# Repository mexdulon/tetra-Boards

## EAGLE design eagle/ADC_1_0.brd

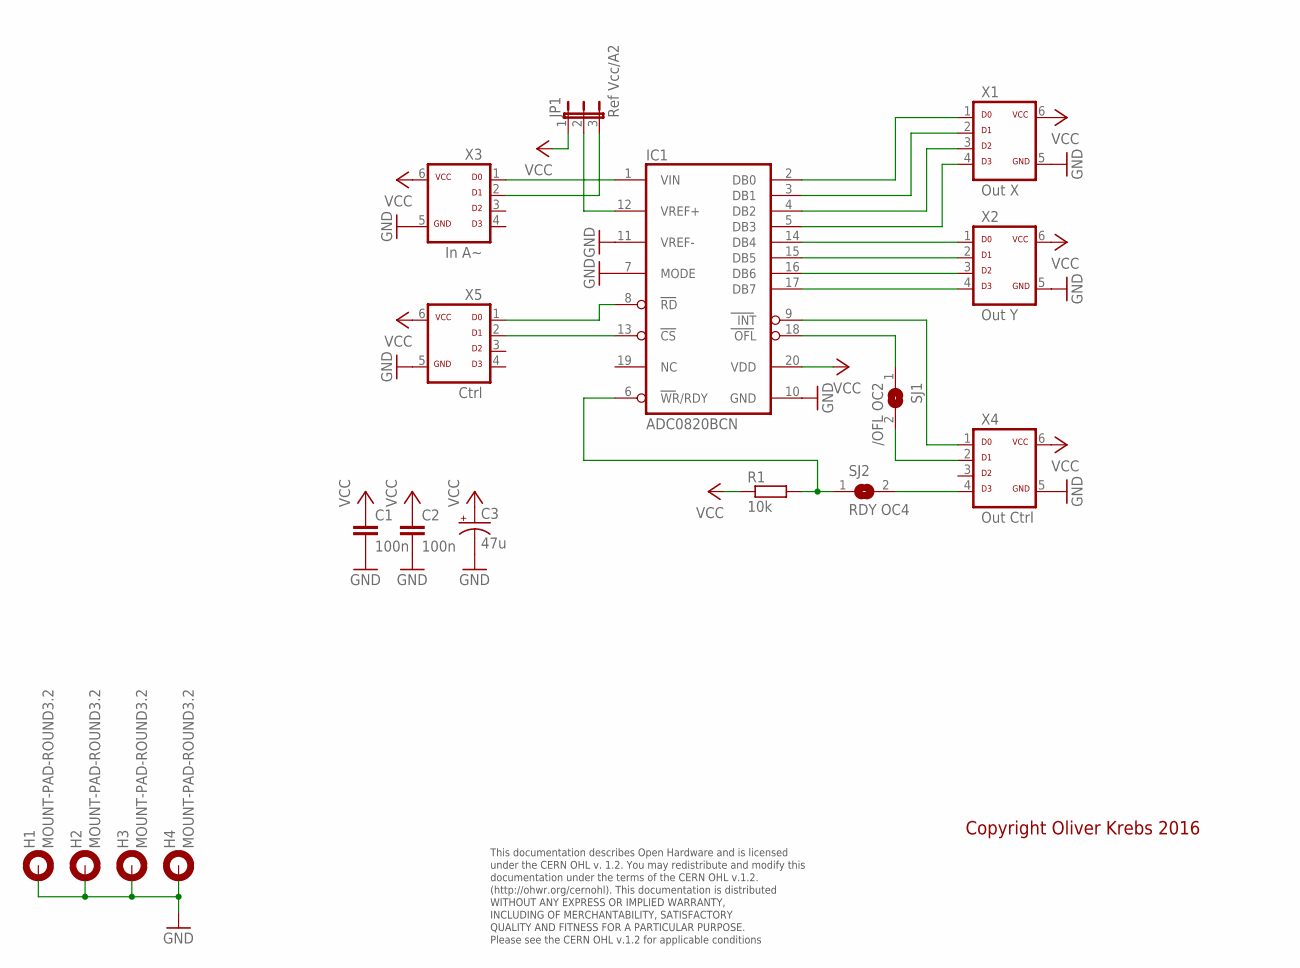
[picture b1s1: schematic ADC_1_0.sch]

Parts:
C1, C2: 100n; CAP-PTH-5MM
C3: 47u; CPOL-RADIAL-100UF-25V
H1, H2, H3, H4: MOUNT-PAD-ROUND3.2; 3,2-PAD
IC1: ADC0820BCN; DIL20
JP1: Ref Vcc/A2; JP2-U
R1: 10k; 0207/10
SJ1: /OFL OC2; SJ
SJ2: RDY OC4; SJ
X1: Out X; ML-6
X2: Out Y; ML-6
X3: In A~; ML-6
X4: Out Ctrl; ML-6
X5: Ctrl; ML-6

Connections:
GND: C1.2, C2.2, C3.2 (-), H1.B3,2, H2.B3,2, H3.B3,2, H4.B3,2, IC1.7 (MODE), IC1.10 (GND), IC1.11 (VREF-), X1.5, X2.5, X3.5, X4.5, X5.5
unnamed: IC1.9 (INT), X4.1
unnamed: SJ1.2, X4.2
unnamed: IC1.2 (DB0), X1.1
unnamed: IC1.3 (DB1), X1.2
unnamed: IC1.4 (DB2), X1.3
unnamed: IC1.5 (DB3), X1.4
unnamed: IC1.14 (DB4), X2.1
unnamed: IC1.15 (DB5), X2.2
unnamed: IC1.16 (DB6), X2.3
unnamed: IC1.17 (DB7), X2.4
unnamed: IC1.1 (VIN), X3.1
unnamed: SJ2.2, X4.4
unnamed: IC1.13 (CS), X5.2
unnamed: IC1.12 (VREF+), JP1.2
unnamed: IC1.8 (RD), X5.1
unnamed: JP1.3, X3.2
unnamed: IC1.6 (WR/RDY), R1.2, SJ2.1
unnamed: IC1.18 (OFL), SJ1.1
VCC: C1.1, C2.1, C3.1 (+), IC1.20 (VDD), JP1.1, R1.1, X1.6, X2.6, X3.6, X4.6, X5.6

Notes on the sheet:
This documentation describes Open Hardware and is licensed under the CERN OHL v. 1.2. You may redistribute and modify this documentation under the terms of the CERN OHL v.1.2. (http://ohwr.org/cernohl). This documentation is distributed WITHOUT ANY EXPRESS OR IMPLIED WARRANTY, INCLUDING OF MERCHANT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
Copyright Oliver Krebs 2016

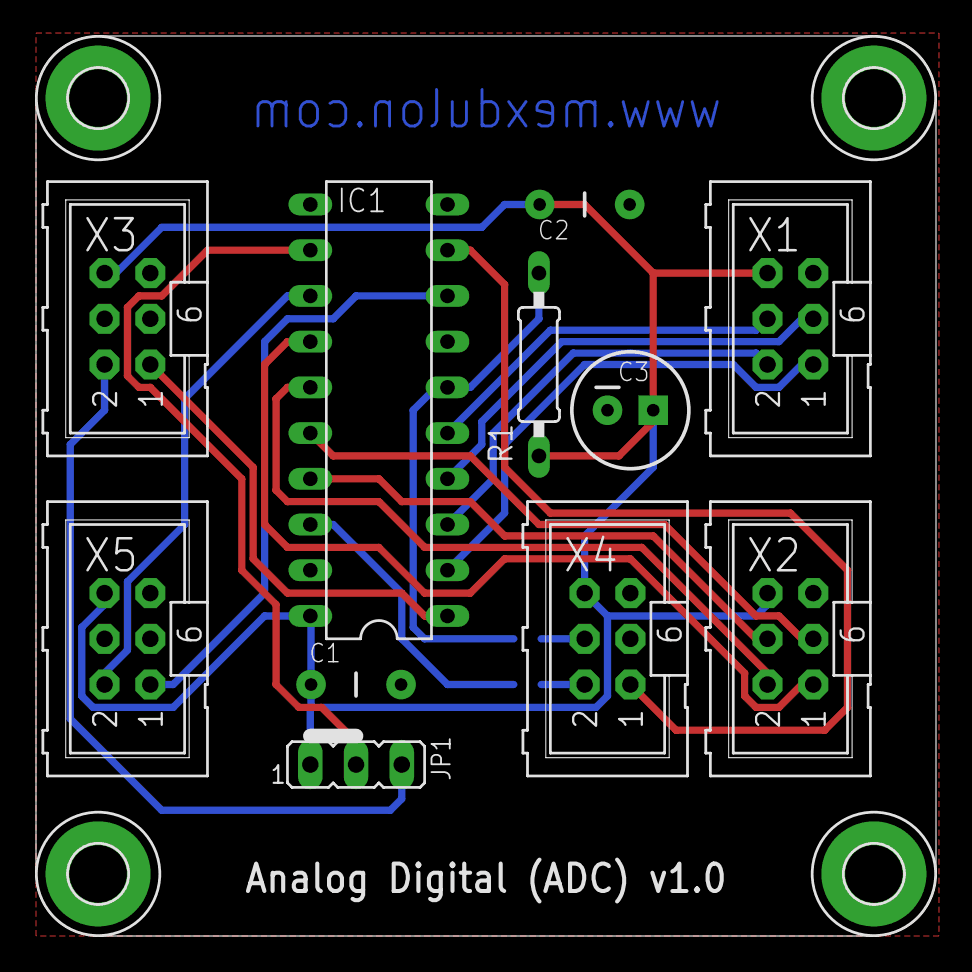
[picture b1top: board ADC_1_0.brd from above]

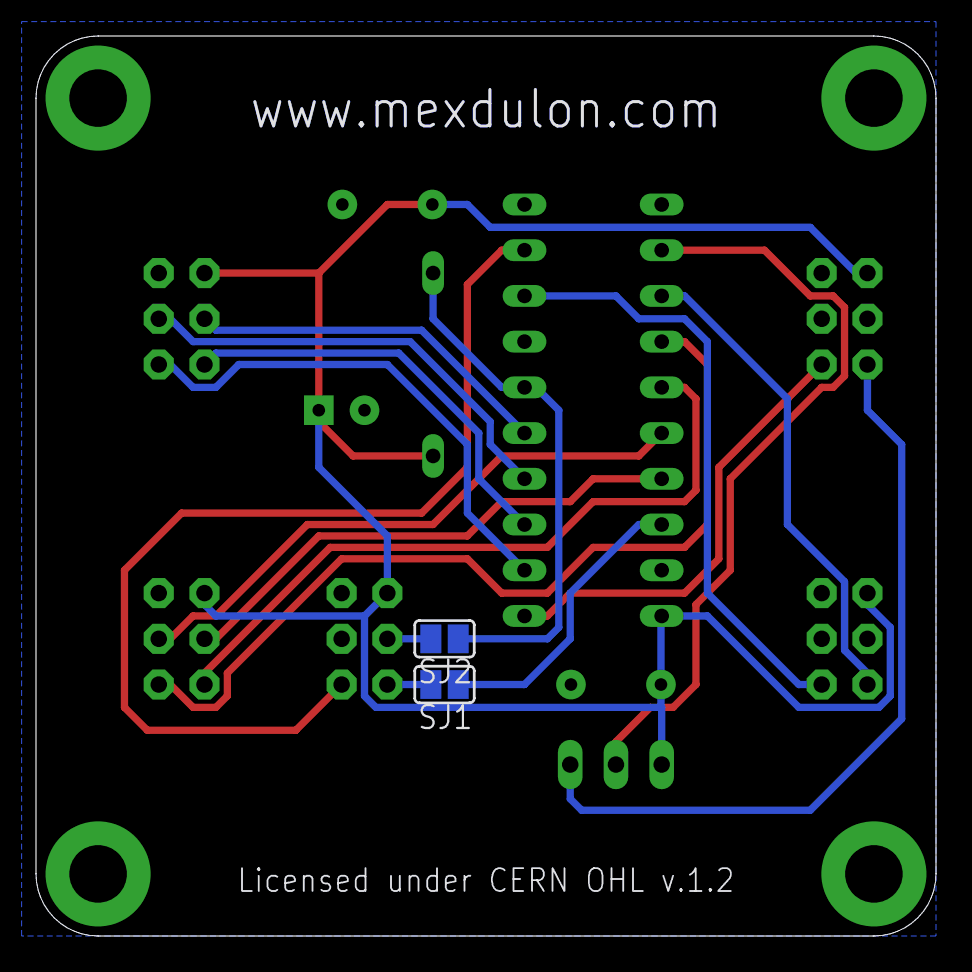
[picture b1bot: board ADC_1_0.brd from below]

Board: 2 copper layers, 50.0 x 50.0 mm, 17 parts (2 on the bottom side), 20 nets.

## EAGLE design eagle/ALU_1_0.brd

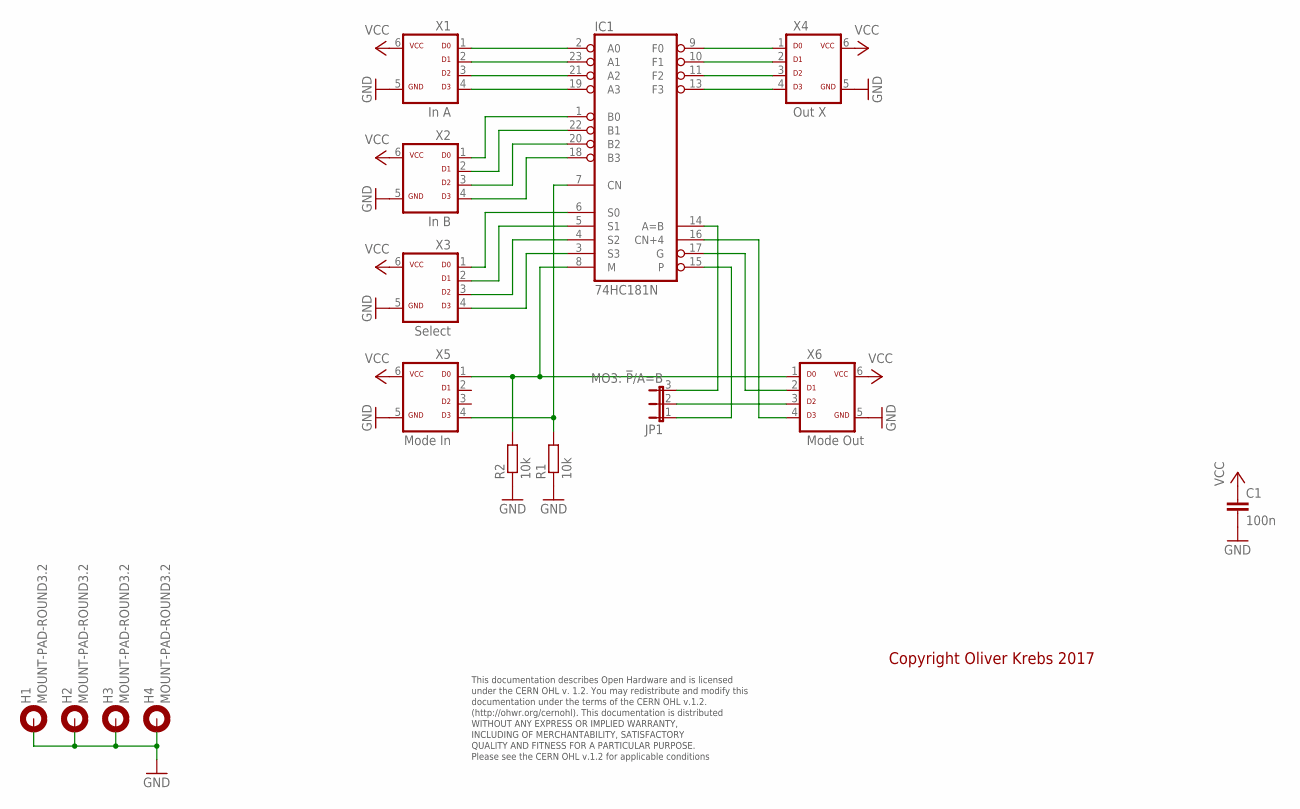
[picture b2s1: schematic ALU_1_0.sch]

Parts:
C1: 100n; C050-025X075
H1, H2, H3, H4: MOUNT-PAD-ROUND3.2; 3,2-PAD
IC1: 74HC181N; DIL24-6
JP1: MO3: !P!/A=B; JP2
R1, R2: 10k; 0207/10
X1: In A; ML-6
X2: In B; ML-6
X3: Select; ML-6
X4: Out X; ML-6
X5: Mode In; ML-6
X6: Mode Out; ML-6

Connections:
GND: C1.2, H1.B3,2, H2.B3,2, H3.B3,2, H4.B3,2, IC1.12 (GND), R1.1, R2.1, X1.5, X2.5, X3.5, X4.5, X5.5, X6.5
unnamed: IC1.9 (F0), X4.1
unnamed: IC1.10 (F1), X4.2
unnamed: IC1.11 (F2), X4.3
unnamed: IC1.13 (F3), X4.4
unnamed: IC1.2 (A0), X1.1
unnamed: IC1.23 (A1), X1.2
unnamed: IC1.21 (A2), X1.3
unnamed: IC1.19 (A3), X1.4
unnamed: IC1.1 (B0), X2.1
unnamed: IC1.22 (B1), X2.2
unnamed: IC1.20 (B2), X2.3
unnamed: IC1.18 (B3), X2.4
unnamed: IC1.6 (S0), X3.1
unnamed: IC1.5 (S1), X3.2
unnamed: IC1.4 (S2), X3.3
unnamed: IC1.3 (S3), X3.4
unnamed: IC1.8 (M), R2.2, X5.1, X6.1
unnamed: IC1.7 (CN), R1.2, X5.4
unnamed: IC1.16 (CN+4), X6.4
unnamed: IC1.15, JP1.1
unnamed: JP1.2, X6.3
unnamed: IC1.14 (A=B), JP1.3
unnamed: IC1.17 (G), X6.2
VCC: C1.1, IC1.24 (VCC), X1.6, X2.6, X3.6, X4.6, X5.6, X6.6

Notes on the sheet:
This documentation describes Open Hardware and is licensed under the CERN OHL v. 1.2. You may redistribute and modify this documentation under the terms of the CERN OHL v.1.2. (http://ohwr.org/cernohl). This documentation is distributed WITHOUT ANY EXPRESS OR IMPLIED WARRANTY, INCLUDING OF MERCHANT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
Copyright Oliver Krebs 2017

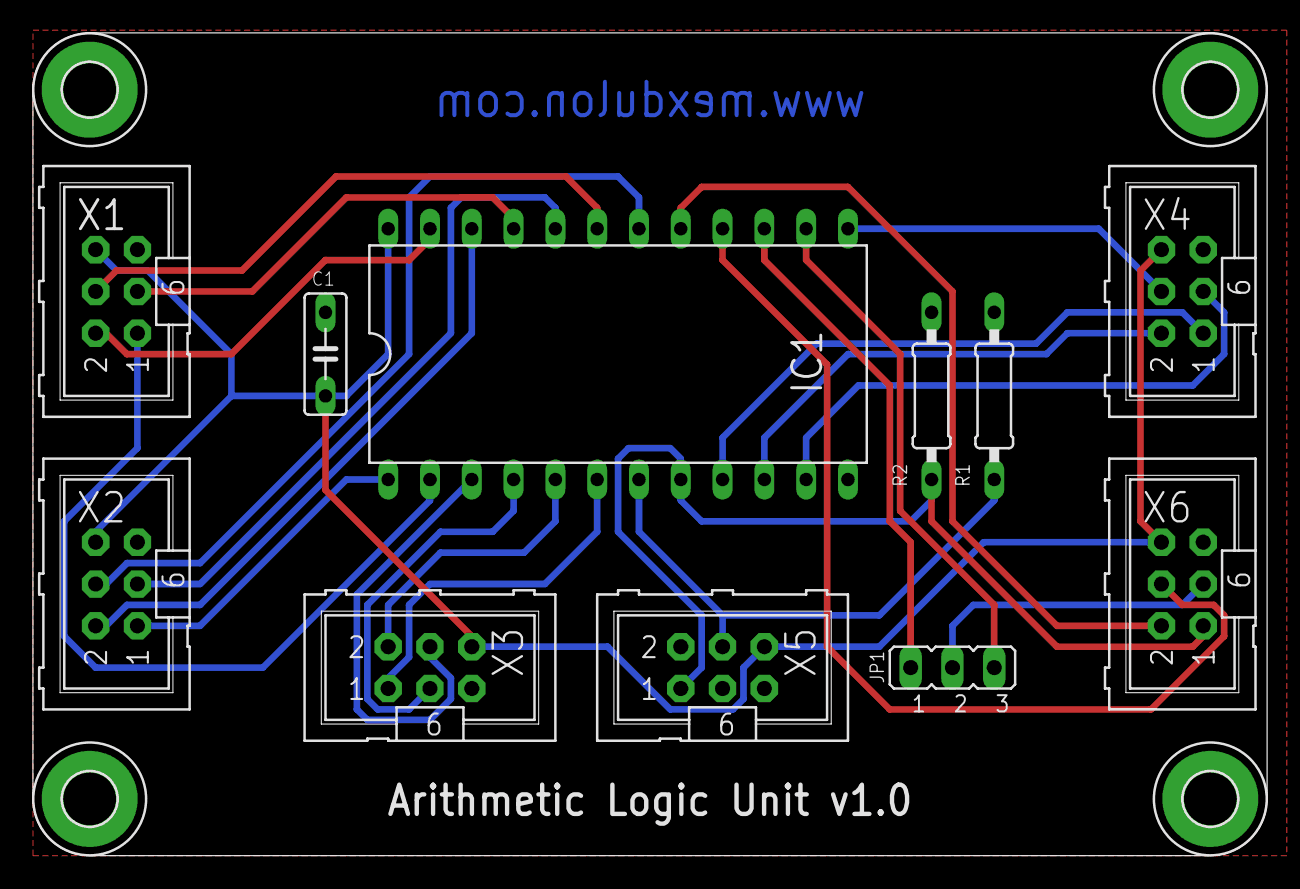
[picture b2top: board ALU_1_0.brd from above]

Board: 2 copper layers, 75.0 x 50.0 mm, 15 parts (0 on the bottom side), 25 nets.

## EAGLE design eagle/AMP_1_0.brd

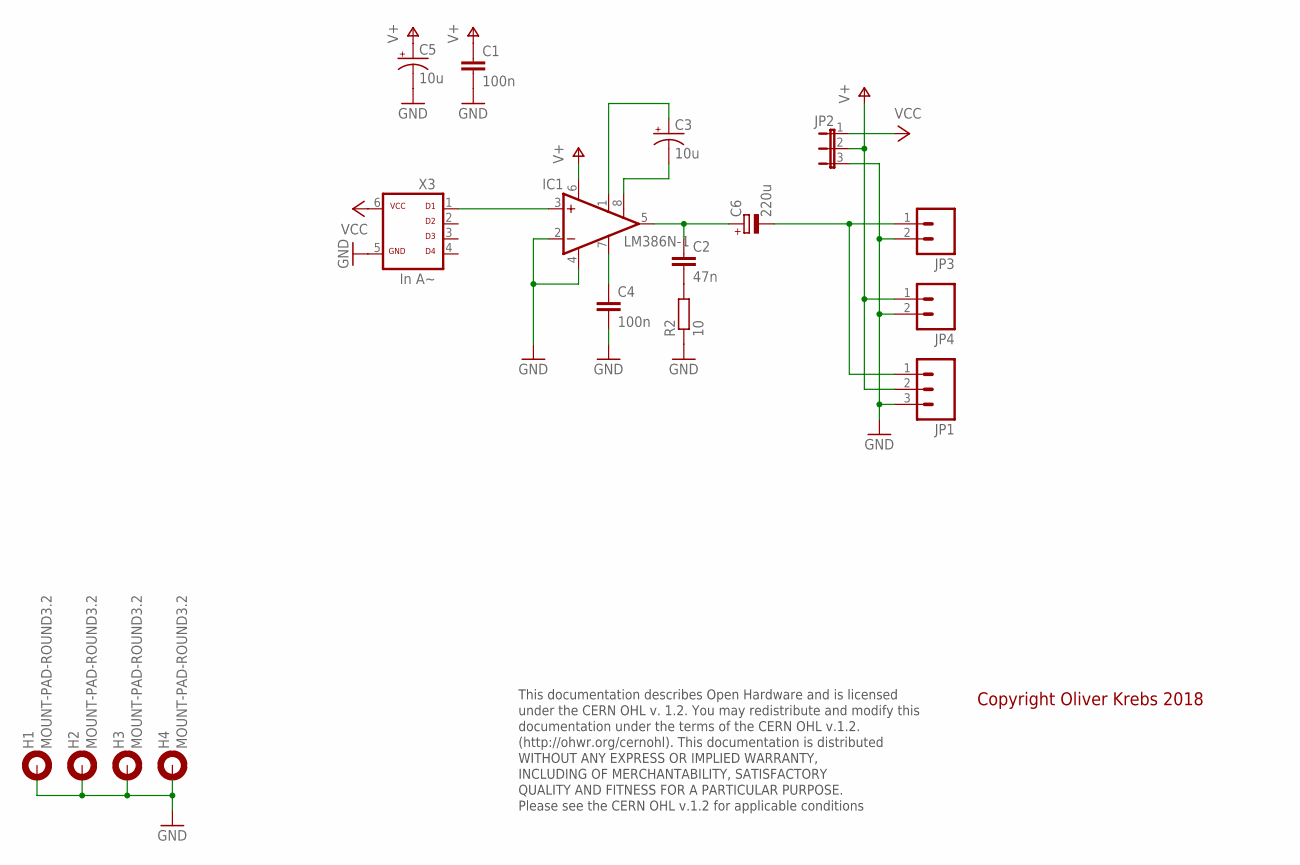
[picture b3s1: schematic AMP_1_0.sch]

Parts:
C1, C4: 100n; C050-025X075
C2: 47n; C050-025X075
C3, C5: 10u; CPOL-RADIAL-10UF-25V
C6: 220u; E3,5-8
H1, H2, H3, H4: MOUNT-PAD-ROUND3.2; 3,2-PAD
IC1: LM386N-1; DIL08
JP1: M03PTH; 1X03
JP2: JP2EJP2-U; JP2-U
JP3, JP4: M021.3MM-5.08; 1X02_BIG_5.08
R2: 10; 0207/10
X3: In A~; ML-6

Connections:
GND: C1.2, C4.2, C5.2 (-), H1.B3,2, H2.B3,2, H3.B3,2, H4.B3,2, IC1.2 (-IN), IC1.4 (GND), JP1.3, JP2.3, JP3.2, JP4.2, R2.1, X3.5
unnamed: C3.2 (-), IC1.8 (GAIN)
unnamed: C3.1 (+), IC1.1 (GAIN)
unnamed: IC1.3 (+IN), X3.1
unnamed: C4.1, IC1.7 (BYPASS)
unnamed: C2.1, C6.+, IC1.5 (OUT)
unnamed: C2.2, R2.2
unnamed: C6.-, JP1.1, JP3.1
V+: C1.1, C5.1 (+), IC1.6 (VS), JP1.2, JP2.2, JP4.1
VCC: JP2.1, X3.6

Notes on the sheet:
This documentation describes Open Hardware and is licensed under the CERN OHL v. 1.2. You may redistribute and modify this documentation under the terms of the CERN OHL v.1.2. (http://ohwr.org/cernohl). This documentation is distributed WITHOUT ANY EXPRESS OR IMPLIED WARRANTY, INCLUDING OF MERCHANT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
Copyright Oliver Krebs 2018

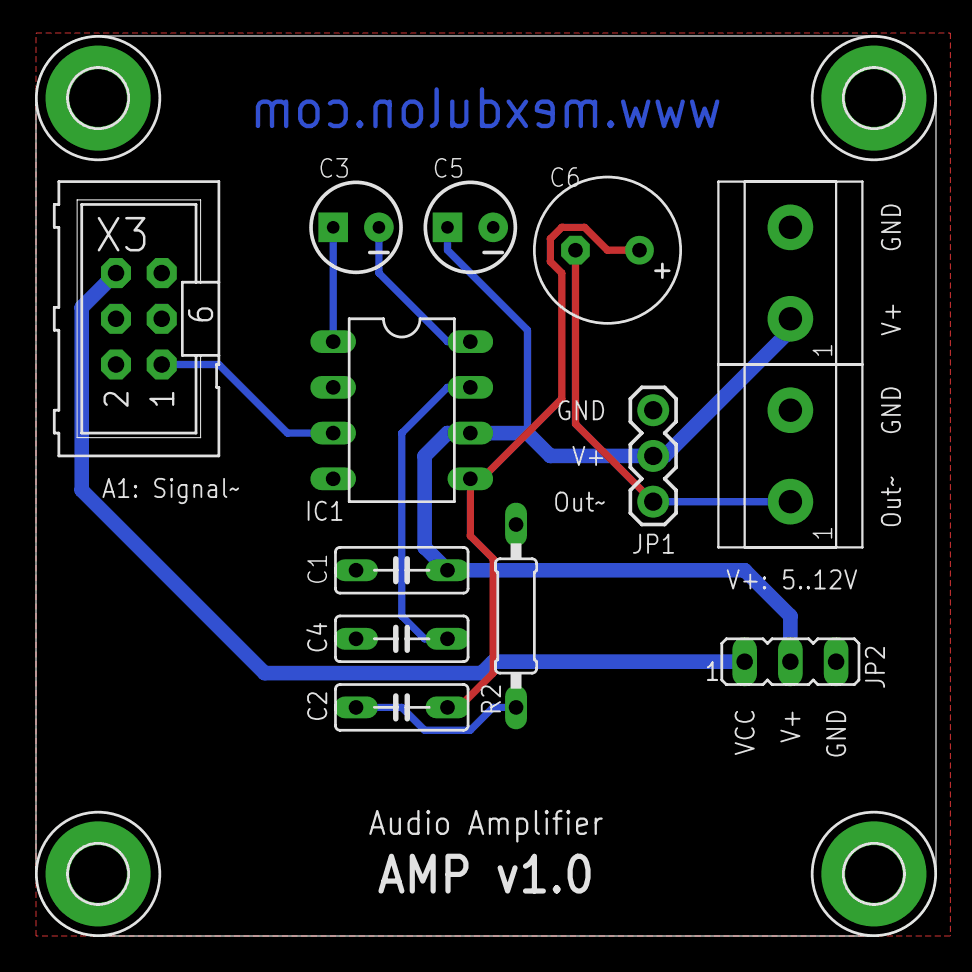
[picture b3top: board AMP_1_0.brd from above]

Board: 2 copper layers, 50.0 x 50.0 mm, 17 parts (0 on the bottom side), 10 nets.

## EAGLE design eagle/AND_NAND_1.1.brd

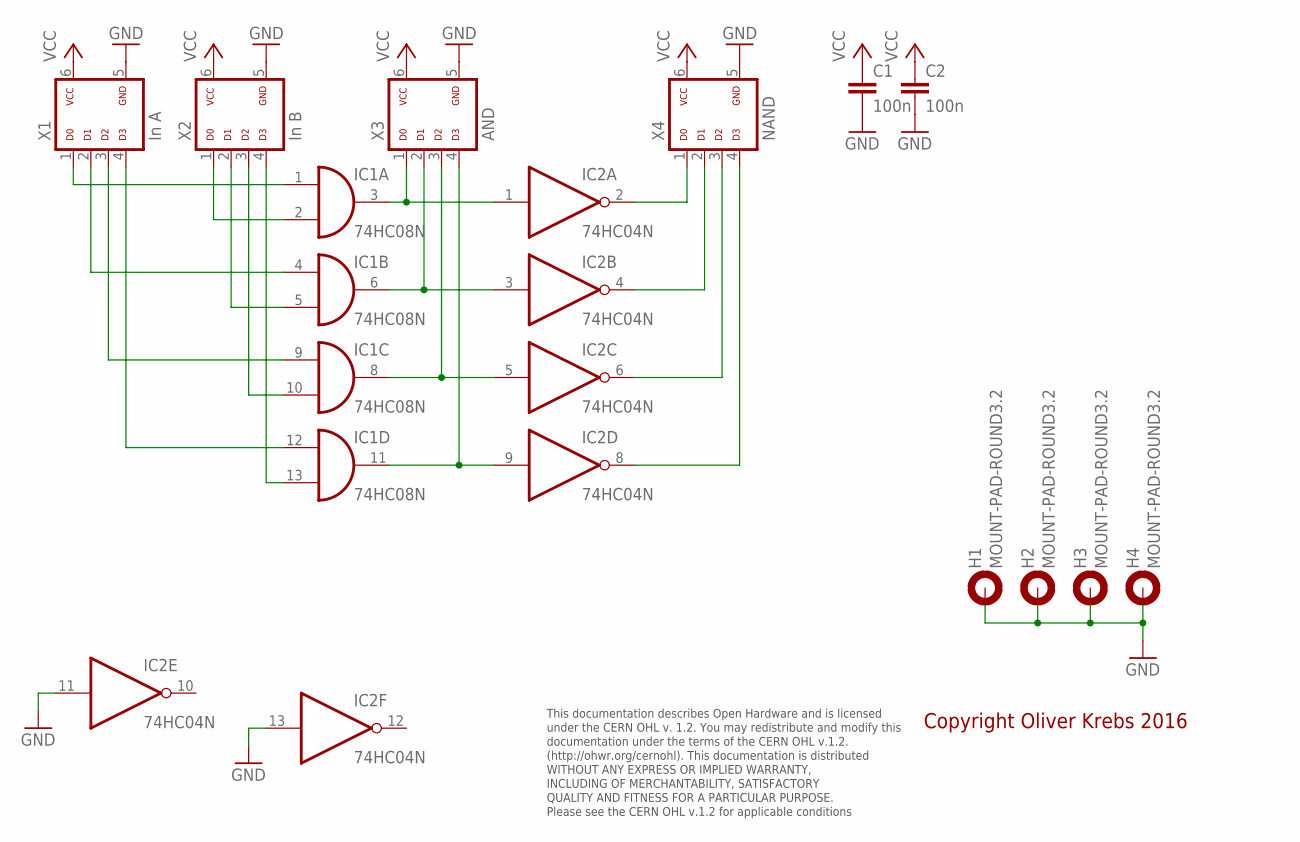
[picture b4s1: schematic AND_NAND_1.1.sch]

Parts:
C1, C2: 100n; C050-025X075
H1, H2, H3, H4: MOUNT-PAD-ROUND3.2; 3,2-PAD
IC1: 74HC08N; DIL14
IC2: 74HC04N; DIL14
X1: In A; ML-6
X2: In B; ML-6
X3: AND; ML-6
X4: NAND; ML-6

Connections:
GND: C1.2, C2.2, H1.B3,2, H2.B3,2, H3.B3,2, H4.B3,2, IC1.7 (GND), IC2.7 (GND), IC2.11 (I), IC2.13 (I), X1.5, X2.5, X3.5, X4.5
unnamed: IC1.3 (O), IC2.1 (I), X3.1
unnamed: IC1.6 (O), IC2.3 (I), X3.2
unnamed: IC1.8 (O), IC2.5 (I), X3.3
unnamed: IC1.11 (O), IC2.9 (I), X3.4
unnamed: IC2.2 (O), X4.1
unnamed: IC2.4 (O), X4.2
unnamed: IC2.6 (O), X4.3
unnamed: IC2.8 (O), X4.4
unnamed: IC1.1 (I0), X1.1
unnamed: IC1.2 (I1), X2.1
unnamed: IC1.5 (I1), X2.2
unnamed: IC1.4 (I0), X1.2
unnamed: IC1.9 (I0), X1.3
unnamed: IC1.10 (I1), X2.3
unnamed: IC1.12 (I0), X1.4
unnamed: IC1.13 (I1), X2.4
VCC: C1.1, C2.1, IC1.14 (VCC), IC2.14 (VCC), X1.6, X2.6, X3.6, X4.6

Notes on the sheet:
This documentation describes Open Hardware and is licensed under the CERN OHL v. 1.2. You may redistribute and modify this documentation under the terms of the CERN OHL v.1.2. (http://ohwr.org/cernohl). This documentation is distributed WITHOUT ANY EXPRESS OR IMPLIED WARRANTY, INCLUDING OF MERCHANT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
Copyright Oliver Krebs 2016

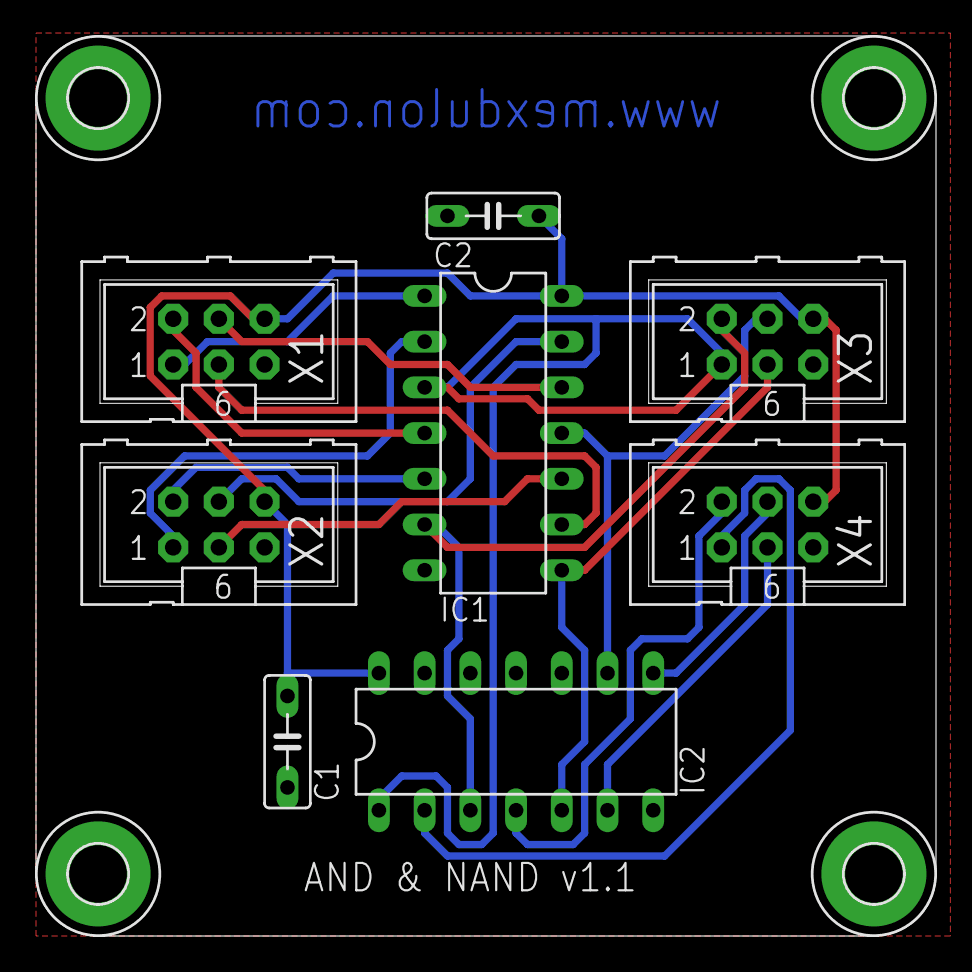
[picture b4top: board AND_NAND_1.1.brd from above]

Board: 2 copper layers, 50.0 x 50.0 mm, 12 parts (0 on the bottom side), 18 nets.

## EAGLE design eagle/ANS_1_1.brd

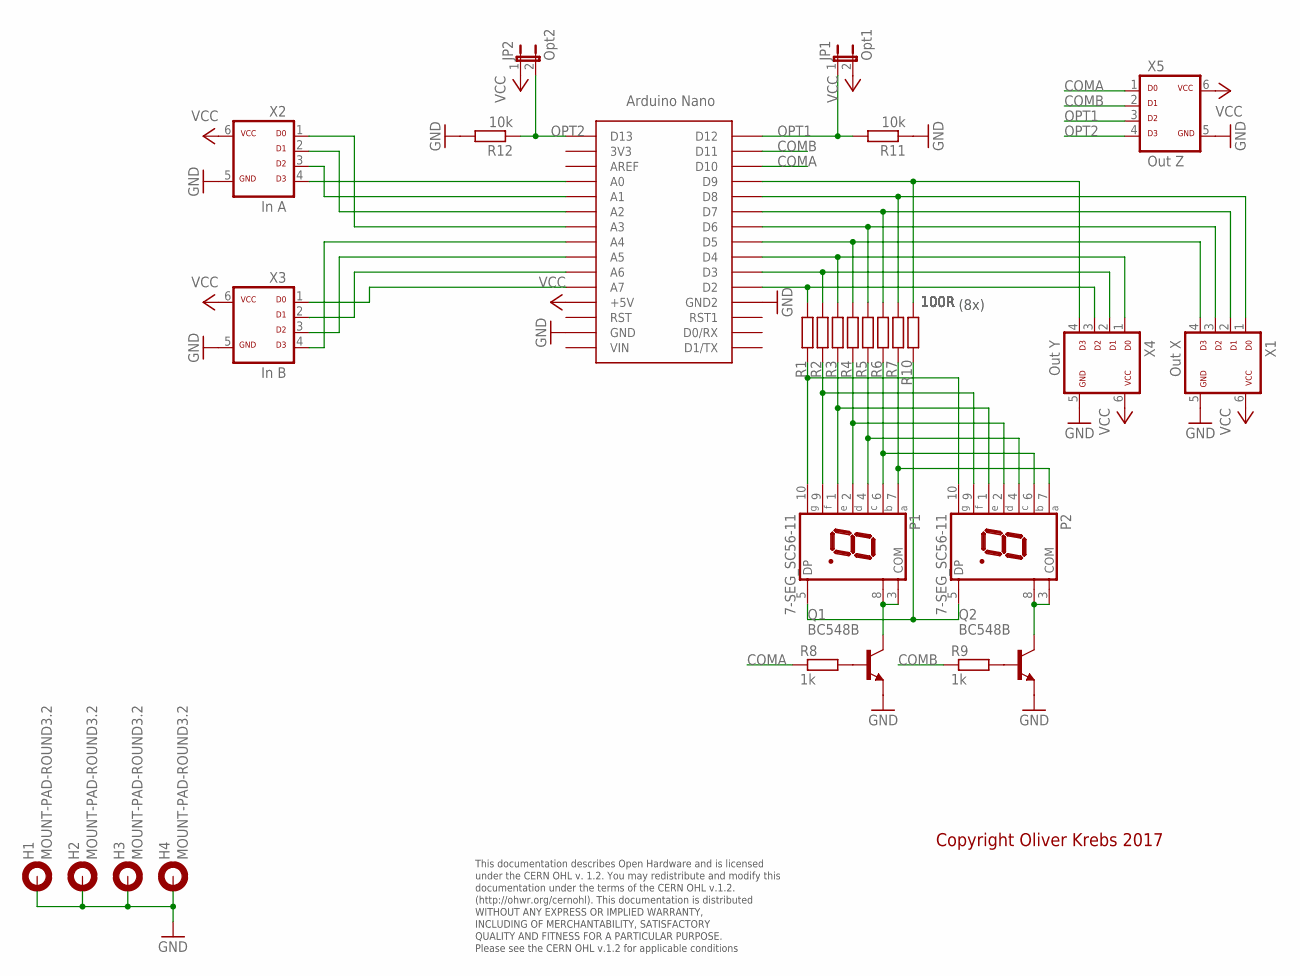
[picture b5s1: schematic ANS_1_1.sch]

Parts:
H1, H2, H3, H4: MOUNT-PAD-ROUND3.2; 3,2-PAD
JP1: Opt1; JP1
JP2: Opt2; JP1
P1, P2: 7-SEG_SC56-11; SA56-11
Q1, Q2: BC548B; TO92-EBC
R1, R2, R3, R4, R5, R6, R7, R10: 100R; 0207/10
R8, R9: 1k; 0207/10
R11, R12: 10k; 0207/10
U$1: NANO
X1: Out X; ML-6
X2: In A; ML-6
X3: In B; ML-6
X4: Out Y; ML-6
X5: Out Z; ML-6

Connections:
COMA: R8.1, U$1.D10, X5.1
COMB: R9.1, U$1.D11, X5.2
GND: H1.B3,2, H2.B3,2, H3.B3,2, H4.B3,2, Q1.E, Q2.E, R11.1, R12.2, U$1.GND, U$1.GND1 (GND2), X1.5, X2.5, X3.5, X4.5, X5.5
unnamed: U$1.A0, X2.4
unnamed: U$1.A1, X2.3
unnamed: U$1.A2, X2.2
unnamed: U$1.A3, X2.1
unnamed: U$1.A4, X3.4
unnamed: U$1.A5, X3.3
unnamed: U$1.A6, X3.2
unnamed: U$1.A7, X3.1
unnamed: P1.10 (G), P2.10 (G), R1.1
unnamed: P1.9 (F), P2.9 (F), R2.1
unnamed: P1.1 (E), P2.1 (E), R3.1
unnamed: P1.2 (D), P2.2 (D), R4.1
unnamed: P1.4 (C), P2.4 (C), R5.1
unnamed: P1.6 (B), P2.6 (B), R6.1
unnamed: P1.7 (A), P2.7 (A), R7.1
unnamed: R1.2, U$1.D2, X4.3
unnamed: R2.2, U$1.D3, X4.2
unnamed: R3.2, U$1.D4, X4.1
unnamed: R4.2, U$1.D5, X1.4
unnamed: R5.2, U$1.D6, X1.3
unnamed: R6.2, U$1.D7, X1.2
unnamed: R7.2, U$1.D8, X1.1
unnamed: P1.3 (COM), P1.8 (COM), Q1.C
unnamed: P2.3 (COM), P2.8 (COM), Q2.C
unnamed: Q1.B, R8.2
unnamed: Q2.B, R9.2
unnamed: R10.2, U$1.D9, X4.4
unnamed: P1.5 (DP), P2.5 (DP), R10.1
OPT1: JP1.1, R11.2, U$1.D12, X5.3
OPT2: JP2.2, R12.1, U$1.D13, X5.4
VCC: JP1.2, JP2.1, U$1.5V (+5V), X1.6, X2.6, X3.6, X4.6, X5.6

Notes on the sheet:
This documentation describes Open Hardware and is licensed under the CERN OHL v. 1.2. You may redistribute and modify this documentation under the terms of the CERN OHL v.1.2. (http://ohwr.org/cernohl). This documentation is distributed WITHOUT ANY EXPRESS OR IMPLIED WARRANTY, INCLUDING OF MERCHANT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
Copyright Oliver Krebs 2017
(8x)

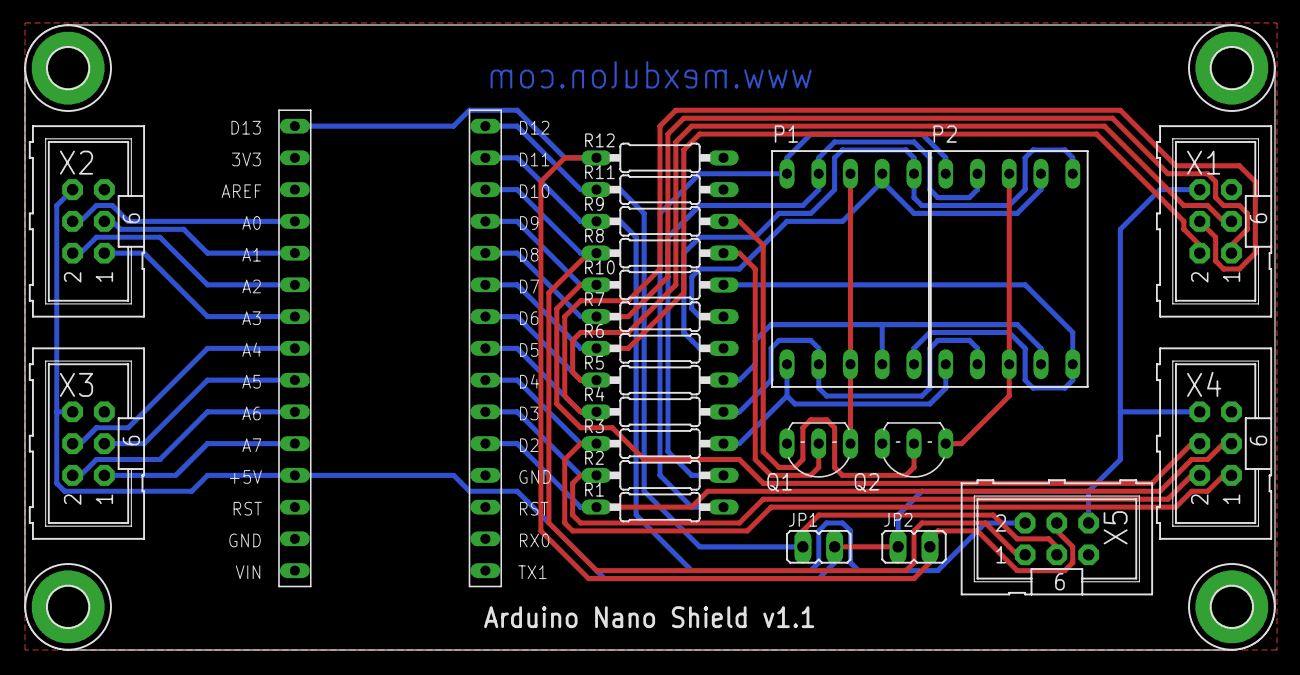
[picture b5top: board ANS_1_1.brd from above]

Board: 2 copper layers, 100.0 x 50.0 mm, 28 parts (0 on the bottom side), 34 nets.

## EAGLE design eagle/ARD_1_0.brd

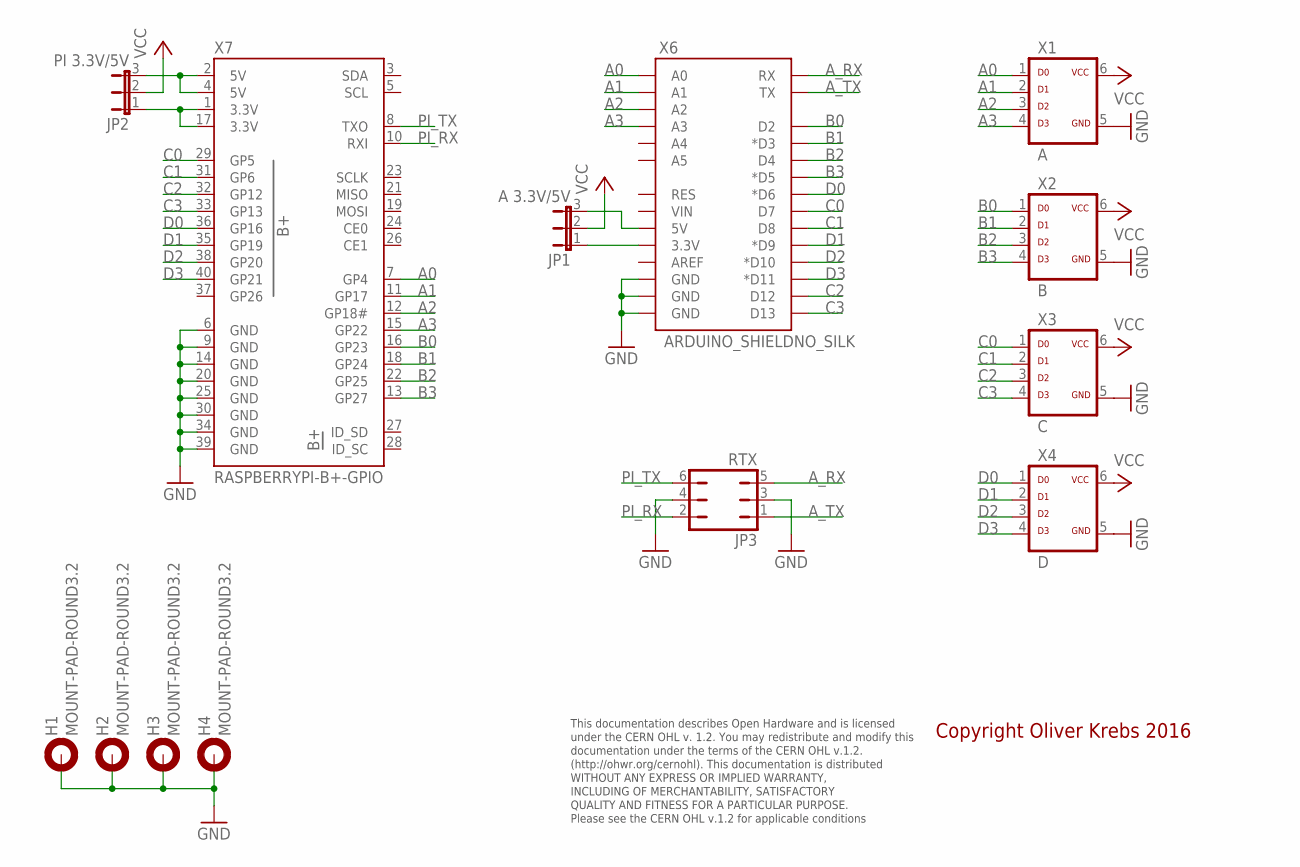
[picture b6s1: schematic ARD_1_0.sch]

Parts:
H1, H2, H3, H4: MOUNT-PAD-ROUND3.2; 3,2-PAD
JP1: A 3.3V/5V; JP2
JP2: PI 3.3V/5V; JP2
JP3: RTX; JP3Q
X1: A; ML-6
X2: B; ML-6
X3: C; ML-6
X4: D; ML-6
X6: ARDUINO_SHIELDNO_SILK; DUEMILANOVE_VIAS
X7: RASPBERRYPI-B+-GPIO; 2X20-SHROUDED

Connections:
A0: X1.1, X6.A0, X7.7 (GP4)
A1: X1.2, X6.A1, X7.11 (GP17)
A2: X1.3, X6.A2, X7.12 (GP18#)
A3: X1.4, X6.A3, X7.15 (GP22)
A_RX: JP3.5, X6.RX
A_TX: JP3.1, X6.TX
B0: X2.1, X6.D2, X7.16 (GP23)
B1: X2.2, X6.D3 (*D3), X7.18 (GP24)
B2: X2.3, X6.D4, X7.22 (GP25)
B3: X2.4, X6.D5 (*D5), X7.13 (GP27)
C0: X3.1, X6.D7, X7.29 (GP5)
C1: X3.2, X6.D8, X7.31 (GP6)
C2: X3.3, X6.D12, X7.32 (GP12)
C3: X3.4, X6.D13, X7.33 (GP13)
D0: X4.1, X6.D6 (*D6), X7.36 (GP16)
D1: X4.2, X6.D9 (*D9), X7.35 (GP19)
D2: X4.3, X6.D10 (*D10), X7.38 (GP20)
D3: X4.4, X6.D11 (*D11), X7.40 (GP21)
GND: H1.B3,2, H2.B3,2, H3.B3,2, H4.B3,2, JP3.3, JP3.4, X1.5, X2.5, X3.5, X4.5, X6.GND@0 (GND), X6.GND@1 (GND), X6.GND@2 (GND), X7.6 (GND), X7.9 (GND), X7.14 (GND), X7.20 (GND), X7.25 (GND), X7.30 (GND), X7.34 (GND), X7.39 (GND)
unnamed: JP2.3, X7.2 (5V), X7.4 (5V)
unnamed: JP2.1, X7.1 (3.3V), X7.17 (3.3V)
unnamed: JP1.1, X6.3.3V
unnamed: JP1.3, X6.5V
PI_RX: JP3.2, X7.10 (RXI)
PI_TX: JP3.6, X7.8 (TXO)
VCC: JP1.2, JP2.2, X1.6, X2.6, X3.6, X4.6

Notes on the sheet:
This documentation describes Open Hardware and is licensed under the CERN OHL v. 1.2. You may redistribute and modify this documentation under the terms of the CERN OHL v.1.2. (http://ohwr.org/cernohl). This documentation is distributed WITHOUT ANY EXPRESS OR IMPLIED WARRANTY, INCLUDING OF MERCHANT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
Copyright Oliver Krebs 2016

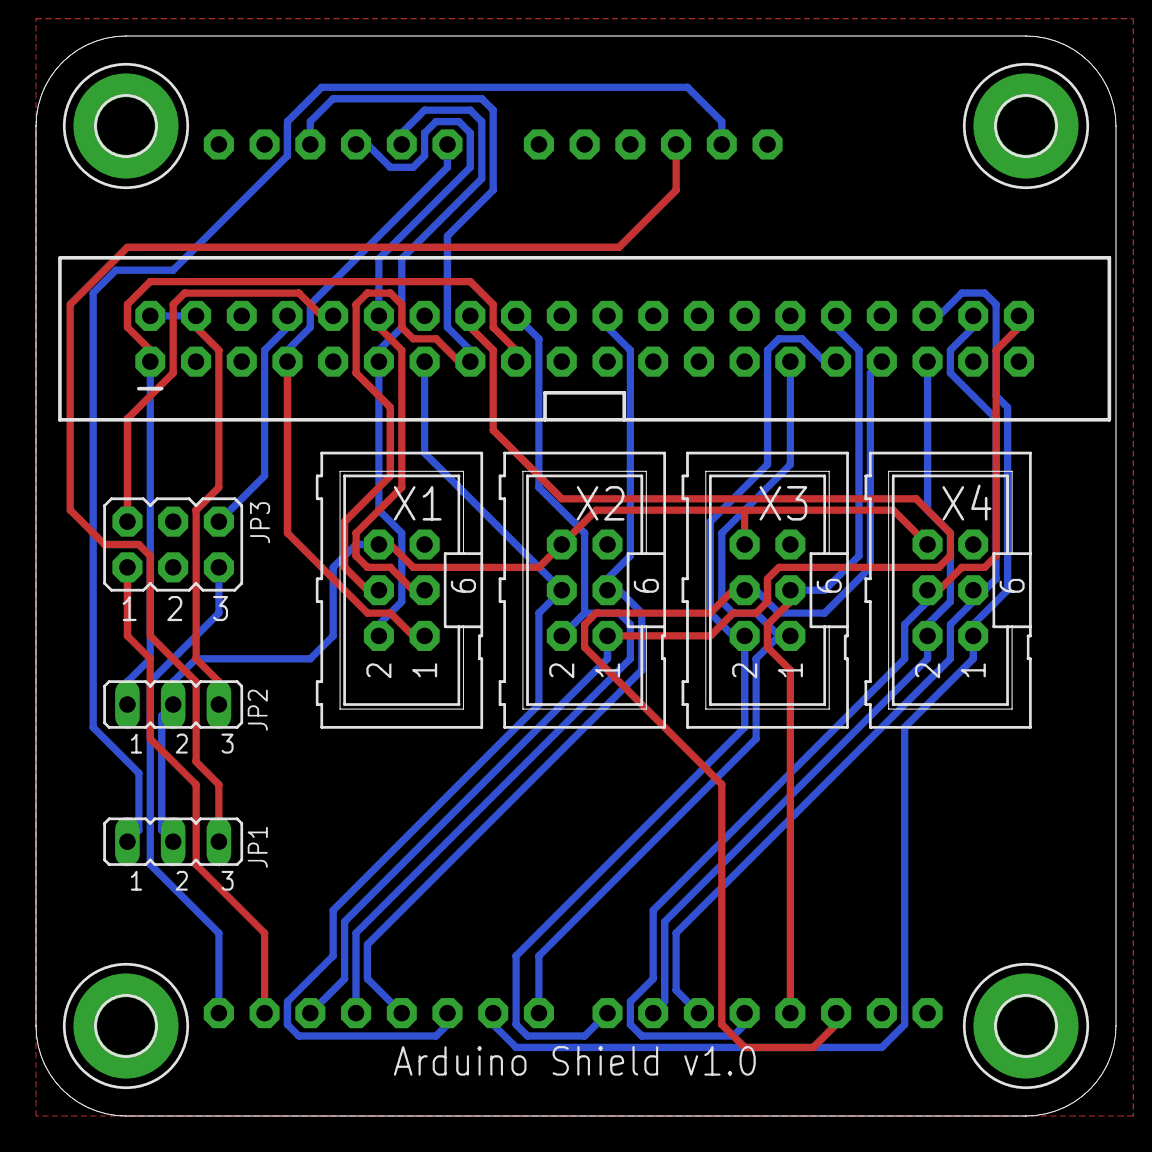
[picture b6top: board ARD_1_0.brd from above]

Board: 2 copper layers, 60.0 x 60.0 mm, 13 parts (0 on the bottom side), 26 nets.

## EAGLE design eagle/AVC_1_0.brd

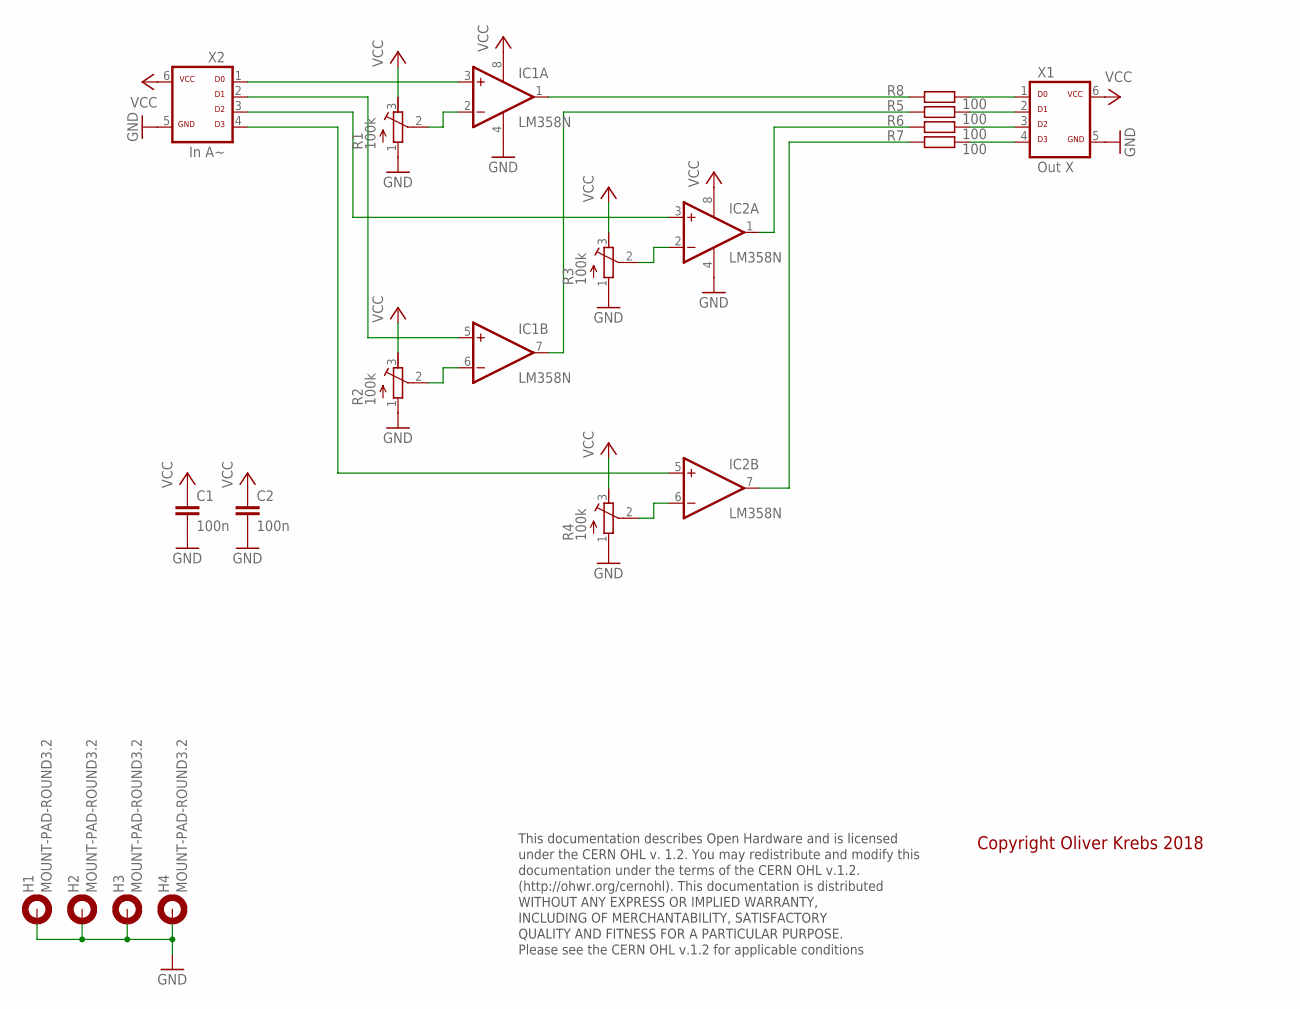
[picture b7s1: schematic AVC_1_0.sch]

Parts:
C1, C2: 100n; C050-025X075
H1, H2, H3, H4: MOUNT-PAD-ROUND3.2; 3,2-PAD
IC1, IC2: LM358N; DIL08
R1, R2, R3, R4: 100k; ACP-6L
R5, R6, R7, R8: 100; 0207/10
X1: Out X; ML-6
X2: In A~; ML-6

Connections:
GND: C1.2, C2.2, H1.B3,2, H2.B3,2, H3.B3,2, H4.B3,2, IC1.4 (V-), IC2.4 (V-), R1.1 (A), R2.1 (A), R3.1 (A), R4.1 (A), X1.5, X2.5
unnamed: IC1.3 (+IN), X2.1
unnamed: IC1.2 (-IN), R1.2 (S)
unnamed: IC1.5 (+IN), X2.2
unnamed: IC1.6 (-IN), R2.2 (S)
unnamed: R5.2, X1.2
unnamed: R8.2, X1.1
unnamed: R6.2, X1.3
unnamed: R7.2, X1.4
unnamed: IC1.1 (OUT), R8.1
unnamed: IC1.7 (OUT), R5.1
unnamed: IC2.3 (+IN), X2.3
unnamed: IC2.2 (-IN), R3.2 (S)
unnamed: IC2.5 (+IN), X2.4
unnamed: IC2.6 (-IN), R4.2 (S)
unnamed: IC2.1 (OUT), R6.1
unnamed: IC2.7 (OUT), R7.1
VCC: C1.1, C2.1, IC1.8 (V+), IC2.8 (V+), R1.3 (E), R2.3 (E), R3.3 (E), R4.3 (E), X1.6, X2.6

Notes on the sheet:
This documentation describes Open Hardware and is licensed under the CERN OHL v. 1.2. You may redistribute and modify this documentation under the terms of the CERN OHL v.1.2. (http://ohwr.org/cernohl). This documentation is distributed WITHOUT ANY EXPRESS OR IMPLIED WARRANTY, INCLUDING OF MERCHANT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
Copyright Oliver Krebs 2018

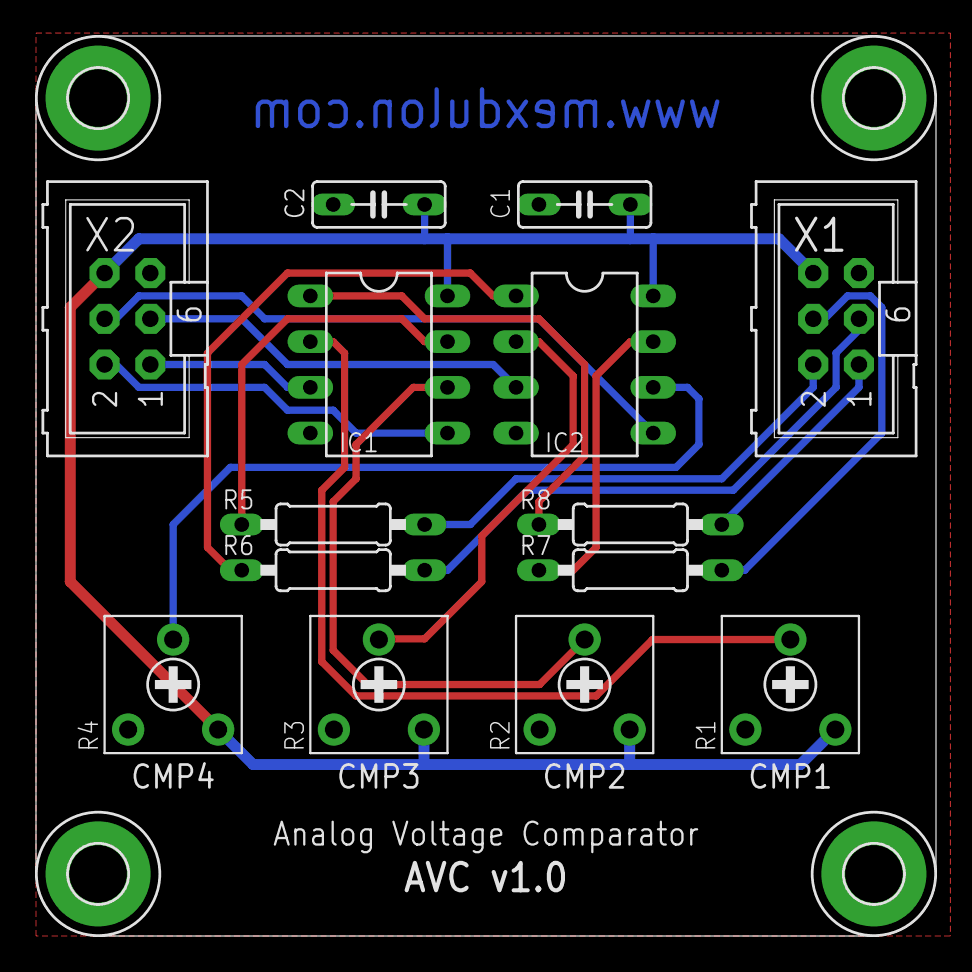
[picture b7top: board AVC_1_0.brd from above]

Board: 2 copper layers, 50.0 x 50.0 mm, 18 parts (0 on the bottom side), 18 nets.

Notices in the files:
eagle/ADC_1_0.brd:
Licensed under CERN OHL v.1.2
parts and their libraries:
SparkFun-Passives: Licensing: Creative Commons ShareAlike 4.0 International - https://creativecommons.org/licenses/by-sa/4.0
